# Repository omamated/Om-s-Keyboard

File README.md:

# My Keyboard

- A custom low-profile wireless mechanical keyboard designed from scratch to match the coolness of the Apple Magic Keyboard while teaching me PCB design, firmware development, and CAD. I know it looks pretty simple, but it took me a long time to make it and I'm pretty proud of it

## Overview

This keyboard is a mechanical and wireless built with the Nice!Nano V2 microcontroller and will use ZMK firmware. My idea was to create a minimal keyboard that matches my dad's MacBook Pro which I occasionally use.

Instead of buying an existing keyboard, I decided to design it myself, so I could learn software like Kicad and Fusion360 more.

The keyboard features:

* Bluetooth connectivity using ZMK firmware
* Nice!Nano V2 controller
* Hot-swappable switches
* Custom Pikachu-themed 3D-printed enclosure
* Rechargeable battery 10000 mah
* Low-profile design

# Why I Built This

I've been using a basic keyboard for a long time and wanted something that felt more premium and minimalist. I wanted something that wasn't that bulky, but still stood out, so I designed the pikachu minamalist keyboard. This keyboard helped me learn major software for the laptop I'm building in the future.

# The Process

## PCB Design

The PCB was designed in KiCad.

Since I was still kinda new to KiCad, I spent a lot of time learning footprint selection, routing techniques, and manufacturing requirements. The PCB includes a way for me to charge a battery using the Nice!Nano. The PCB also uses a matrix to make all the switches fit. 

### Final PCB image

## Schematic Design

The schematic wasn't that bad for me to do as I learned a decent amount from my macropad, so I didn't spend most of my time here. Most of my time was spent on finding the right symbols. I later learned that the symbol doesn't matter at all if you have the right footprint.

### Final Schematic images

## Case Design

The enclosure was designed in Fusion 360. My initial design was very basic, practically just a box with screws.

### Version 2

After reviewing the first version, I increased the case thickness and improved the mounting system. I added thicker walls as the thin walls would lead to snapping.

### Version 3 
Made the case a whole pikachu theme, I will print this in yellow to make it something unique to me. I also added a honey comb pattern at the bottom. To me, this was by far the best version and the one I'm the most proud of.

# Manufacturing Plan

The keyboard will be assembled using the following process. You will first need to order the PCB and all of the otherb parts in the BOM. Once you recieve all the parts and the PCB, you can start soldering them all and then you can flash ZMK software onto the Nice!Nano. Once thats working you can assemble the case, which means you need to put the heat inserts and screw it together.

# Problems

This project made me learn plenty of things that I didn't know very well before.

### Learning KiCad

Although I had some previous experience creating a macropad, this wass my first PCB project without a tutorial

### Routing the PCB

I had to route the PCB about 5 times as it was very confusing to do.

# What I Learned

Through this project I learned how to use PCB design softwares better, how to use ZMK, and how to use fusion 360 efficiently.

# Resources

The following resources were especially helpful during development:

### PCB Design

https://www.youtube.com/watch?v=7UXsD7nSfDY

### Keyboard Design

ScottO'KeeBs YouTube Channel

### Software
 I used Kicad, Fusion360, and ZMK

---

# Bill of Materials
(links are in BOM.csv)

| Item                       | Cost      | Quantity                    |
| -------------------------- | --------- | --------------------------- |
| Low Profile Switches       | $15       | 80                          |
| Nice!Nano V2               | $25       | 1                           |
| Diodes                     | $6        | 80 (only packs of ten)      |
| Custom Keyboard PCB        | $30       | 1 (Minimum order is 5)      |
| Hot-swap Sockets           | $12       | 80                          |
| Power Switch               | $1.50     | 1 (minimum order is 2)      |
| Battery Jack               | $1        | 1 (minimum order is 2)      |
| Battery                    | $7        | 1                           |
| Filament for Case          | $20       | 1                           |
| Heat Inserts & Screws      | $8        | 1 (M2.5 should work)        |

Estimated Total: $136 (before tax + Shipping)

---

# Future Improvements

Potential future upgrades include:

* CNC (I think) enclosure
* Magnetic charging system (maybe for me to use in a custom laptop I'm designing?)
* Lower-profile enclosure revisions
* Improved battery mounting
* Custom keycaps

# Gallery/Images

### PCB Render

Although it is quite tight the hot-swap pocket does fit under the Nice nano, which I anticipated as per my resources.

### Schematic

### Updated Case

### Zine Page

Ok look, my Zine was saved in canva (under my school account), so it was hard for me to add the new case on the back side, so I hope y'all will let it slide.

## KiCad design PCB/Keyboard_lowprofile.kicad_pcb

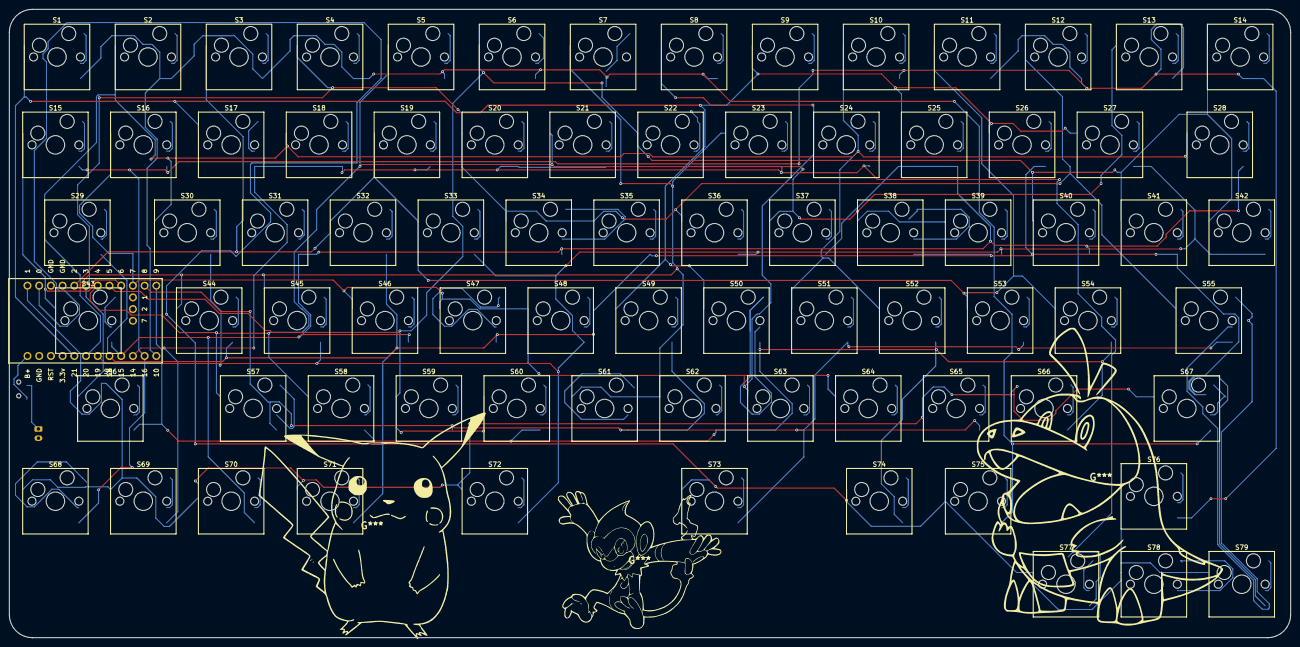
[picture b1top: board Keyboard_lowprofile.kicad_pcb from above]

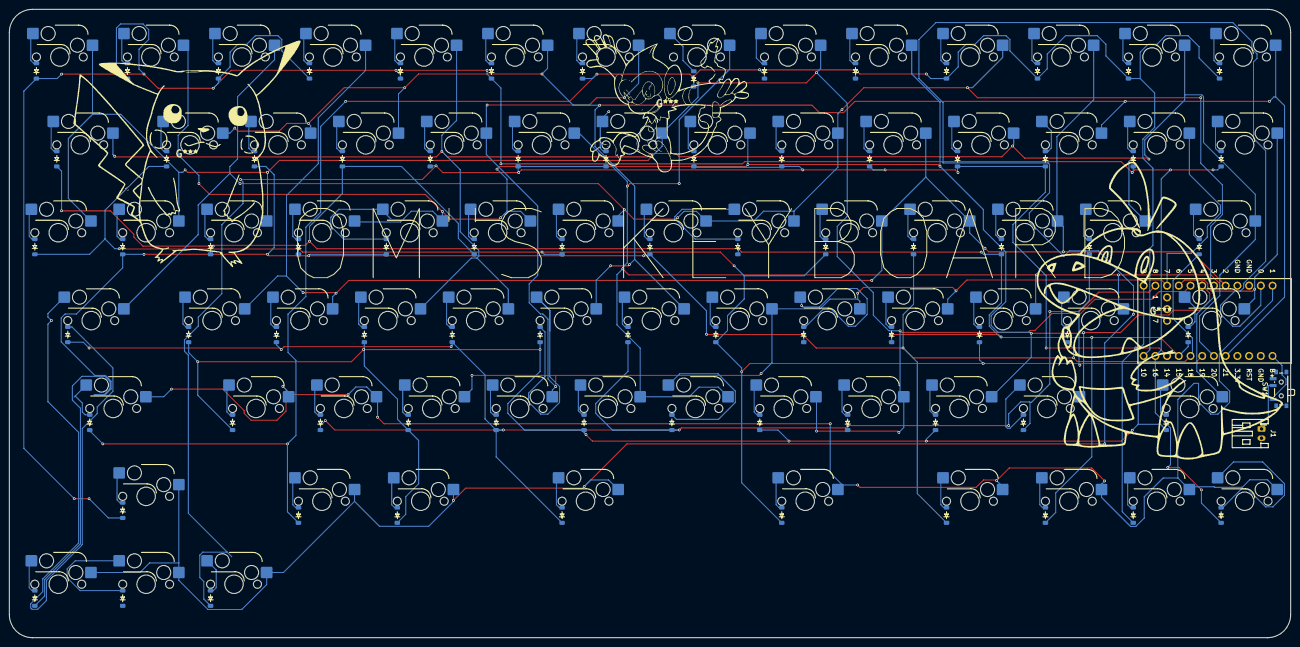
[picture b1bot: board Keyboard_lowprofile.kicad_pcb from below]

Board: 2 copper layers, 277.8 x 136.2 mm, 161 parts (82 on the bottom side), 99 nets.

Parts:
D1, D2, D3, D4, D5, D6, D7, D8, D9, D10, D11, D12, D13, D14, D15, D16, D17, D18, D19, D20, D21, D22, D23, D24, D25, D26, D27, D28, D29, D30, D31, D32, D33, D34, D35, D36, D37, D38, D39, D40, D41, D42, D43, D44, D45, D46, D47, D48, D49, D50, D51, D52, D53, D54, D55, D56, D57, D58, D59, D60, D61, D62, D63, D64, D65, D66, D67, D68, D69, D70, D71, D72, D73, D74, D75, D76, D77, D78, D79: Diode_SOD-123
J1: Conn_01x02_Socket; JST_PH_S2B-PH-K_1x02_P2.00mm_Horizontal
S1, S2, S3, S4, S5, S6, S7, S8, S9, S10, S11, S12, S13, S14, S15, S16, S17, S18, S19, S20, S21, S22, S23, S24, S25, S26, S27, S28, S29, S30, S31, S32, S33, S34, S35, S36, S37, S38, S39, S40, S41, S42, S43, S44, S45, S46, S47, S48, S49, S50, S51, S52, S53, S54, S55, S56, S57, S58, S59, S60, S61, S62, S63, S64, S65, S66, S67, S68, S69, S70, S71, S72, S73, S74, S75, S76, S77, S78, S79: Hotswap_MX_1.00u
SW1: SW_SPDT_312; SW_SPDT_PCM12
U1: Nice_Nano_V2

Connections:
Column 0: S1.1, S9.1, S17.1, S25.1, S26.1, S27.1, S49.1, S50.1, U1.20 (21)
Column 1: S2.1, S10.1, S18.1, S28.1, S29.1, S30.1, S51.1, S52.1, U1.19 (20)
Column 2: S3.1, S11.1, S19.1, S31.1, S32.1, S33.1, S53.1, S54.1, U1.5 (2)
Column 3: S4.1, S12.1, S20.1, S34.1, S35.1, S36.1, S55.1, S56.1, U1.6 (3)
Column 4: S5.1, S13.1, S21.1, S37.1, S38.1, S39.1, S57.1, S58.1, U1.7 (4)
Column 5: S6.1, S14.1, S22.1, S40.1, S41.1, S42.1, S59.1, S60.1, U1.8 (5)
Column 6: S7.1, S15.1, S23.1, S43.1, S44.1, S45.1, S61.1, S62.1, U1.9 (6)
Column 7: S8.1, S16.1, S24.1, S46.1, S47.1, S48.1, S63.1, S64.1, U1.10 (7)
Column 8: S65.1, S66.1, S67.1, S68.1, S69.1, S70.1, S71.1, S72.1, U1.1
Column 9: S73.1, S74.1, S75.1, S76.1, S77.1, S78.1, S79.1, U1.2 (0)
unnamed: D1.2 (A), S1.2
unnamed: D2.2 (A), S2.2
unnamed: D3.2 (A), S3.2
unnamed: D4.2 (A), S4.2
unnamed: D5.2 (A), S5.2
unnamed: D6.2 (A), S6.2
unnamed: D7.2 (A), S7.2
unnamed: D8.2 (A), S8.2
unnamed: D9.2 (A), S9.2
unnamed: D10.2 (A), S10.2
unnamed: D11.2 (A), S11.2
unnamed: D12.2 (A), S12.2
unnamed: D13.2 (A), S13.2
unnamed: D14.2 (A), S14.2
unnamed: D15.2 (A), S15.2
unnamed: D16.2 (A), S16.2
unnamed: D17.2 (A), S17.2
unnamed: D18.2 (A), S18.2
unnamed: D19.2 (A), S19.2
unnamed: D20.2 (A), S20.2
unnamed: D21.2 (A), S21.2
unnamed: D22.2 (A), S22.2
unnamed: D23.2 (A), S23.2
unnamed: D24.2 (A), S24.2
unnamed: D25.2 (A), S25.2
unnamed: D26.2 (A), S26.2
unnamed: D27.2 (A), S27.2
unnamed: D28.2 (A), S28.2
unnamed: D29.2 (A), S29.2
unnamed: D30.2 (A), S30.2
unnamed: D31.2 (A), S31.2
unnamed: D32.2 (A), S32.2
unnamed: D33.2 (A), S33.2
unnamed: D34.2 (A), S34.2
unnamed: D35.2 (A), S35.2
unnamed: D36.2 (A), S36.2
unnamed: D37.2 (A), S37.2
unnamed: D38.2 (A), S38.2
unnamed: D39.2 (A), S39.2
unnamed: D40.2 (A), S40.2
unnamed: D41.2 (A), S41.2
unnamed: D42.2 (A), S42.2
unnamed: D43.2 (A), S43.2
unnamed: D44.2 (A), S44.2
unnamed: D45.2 (A), S45.2
unnamed: D46.2 (A), S46.2
unnamed: D47.2 (A), S47.2
unnamed: D48.2 (A), S48.2
unnamed: D49.2 (A), S49.2
unnamed: D50.2 (A), S50.2
unnamed: D51.2 (A), S51.2
unnamed: D52.2 (A), S52.2
unnamed: D53.2 (A), S53.2
unnamed: D54.2 (A), S54.2
unnamed: D55.2 (A), S55.2
unnamed: D56.2 (A), S56.2
unnamed: D57.2 (A), S57.2
unnamed: D58.2 (A), S58.2
unnamed: D59.2 (A), S59.2
unnamed: D60.2 (A), S60.2
unnamed: D61.2 (A), S61.2
unnamed: D62.2 (A), S62.2
unnamed: D63.2 (A), S63.2
unnamed: D64.2 (A), S64.2
unnamed: D65.2 (A), S65.2
unnamed: D66.2 (A), S66.2
unnamed: D67.2 (A), S67.2
unnamed: D68.2 (A), S68.2
unnamed: D69.2 (A), S69.2
unnamed: D70.2 (A), S70.2
unnamed: D71.2 (A), S71.2
unnamed: D72.2 (A), S72.2
unnamed: D73.2 (A), S73.2
unnamed: D74.2 (A), S74.2
unnamed: D75.2 (A), S75.2
unnamed: D76.2 (A), S76.2
unnamed: D77.2 (A), S77.2
unnamed: D78.2 (A), S78.2
unnamed: D79.2 (A), S79.2
unnamed: J1.1, SW1.2 (C)
unnamed: SW1.1 (B), U1.24 (B+)
Row 0: D49.1 (K), D51.1 (K), D53.1 (K), D55.1 (K), D57.1 (K), D59.1 (K), D61.1 (K), D63.1 (K), D65.1 (K), D73.1 (K), U1.11 (8)
Row 1: D50.1 (K), D52.1 (K), D54.1 (K), D56.1 (K), D58.1 (K), D60.1 (K), D62.1 (K), D64.1 (K), D66.1 (K), D74.1 (K), U1.12 (9)
Row 2: D1.1 (K), D2.1 (K), D3.1 (K), D4.1 (K), D5.1 (K), D6.1 (K), D7.1 (K), D8.1 (K), D67.1 (K), D75.1 (K), U1.13 (10)
Row 3: D9.1 (K), D10.1 (K), D11.1 (K), D12.1 (K), D13.1 (K), D14.1 (K), D15.1 (K), D16.1 (K), D68.1 (K), D76.1 (K), U1.14 (16)
Row 4: D17.1 (K), D18.1 (K), D19.1 (K), D20.1 (K), D21.1 (K), D22.1 (K), D23.1 (K), D24.1 (K), D69.1 (K), D77.1 (K), U1.15 (14)
Row 5: D25.1 (K), D28.1 (K), D31.1 (K), D34.1 (K), D37.1 (K), D40.1 (K), D43.1 (K), D46.1 (K), D70.1 (K), U1.16 (15)
Row 6: D26.1 (K), D29.1 (K), D32.1 (K), D35.1 (K), D38.1 (K), D41.1 (K), D44.1 (K), D47.1 (K), D71.1 (K), D79.1 (K), U1.17 (18)
Row 7: D27.1 (K), D30.1 (K), D33.1 (K), D36.1 (K), D39.1 (K), D42.1 (K), D45.1 (K), D48.1 (K), D72.1 (K), U1.18 (19)

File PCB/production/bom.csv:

Designator,Footprint,Quantity,Value,LCSC Part #
"D1, D10, D11, D12, D13, D14, D15, D16, D17, D18, D19, D2, D20, D21, D22, D23, D24, D25, D26, D27, D28, D29, D3, D30, D31, D32, D33, D34, D35, D36, D37, D38, D39, D4, D40, D41, D42, D43, D44, D45, D46, D47, D48, D49, D5, D50, D51, D52, D53, D54, D55, D56, D57, D58, D59, D6, D60, D61, D62, D63, D64, D65, D66, D67, D68, D69, D7, D70, D71, D72, D73, D74, D75, D76, D77, D78, D79, D8, D9",Diode_SOD-123,79,~,
J1,JST_PH_S2B-PH-K_1x02_P2.00mm_Horizontal,1,Conn_01x02_Socket,
"S1, S10, S11, S12, S13, S14, S15, S16, S17, S18, S19, S2, S20, S21, S22, S23, S24, S25, S26, S27, S28, S29, S3, S30, S31, S32, S33, S34, S35, S36, S37, S38, S39, S4, S40, S41, S42, S43, S44, S45, S46, S47, S48, S49, S5, S50, S51, S52, S53, S54, S55, S56, S57, S58, S59, S6, S60, S61, S62, S63, S64, S65, S66, S67, S68, S69, S7, S70, S71, S72, S73, S74, S75, S76, S77, S78, S79, S8, S9",Hotswap_MX_1.00u,79,~,
SW1,SW_SPDT_PCM12,1,SW_SPDT_312,
U1,Nice_Nano_V2,1,Nice_Nano_V2,

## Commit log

2026-02-01 Update README with project details and parts list
    Expanded the project description and added a detailed bill of parts with links and prices.
2026-02-01 Refactor links in README for consistency
    Updated links in the README to use a consistent format.
2026-02-01 Update README to include bill of parts section
    Added a section for the bill of parts with a link.
2026-02-01 Fix link formatting in README.md
2026-02-01 Update link text for design document in README
2026-02-01 Create sadf
2026-02-01 PCB Files
2026-02-01 Add images for final PCB and schematic
    Added images for final PCB, schematic, and 3D viewer.
2026-02-01 Gerber file
2026-02-01 Create adsf
2026-02-01 Add Fusion 360 case image to README
    Added an image of the Fusion 360 case to the README.
2026-02-07 Fix tutorial links formatting in README
    Corrected formatting issues with tutorial links in the README.
2026-02-07 Fix links in README.md for tutorials
2026-02-07 Fix link formatting for scottokeebs in README
2026-02-07 Update README with project completion details
    Added personal experience and time taken for project completion.
2026-02-21 Add ZMK configuration for keyboard layout
2026-02-21 added files
2026-02-21 BBOM
2026-02-22 changed cad
2026-02-22 Revise README with assembly details and formatting
    Updated the README to include planned assembly details and improved formatting.
2026-02-28 Add item list with costs and links to README
2026-02-28 Add BOM with item details and costs
2026-02-28 Update README.md file with new content
2026-03-21 better cad
    ADDED SCREW HOLES
2026-03-27 added source files
2026-03-27 added images to readme for screwholes in the case
2026-03-31 Readem fixed
2026-03-31 images in readme
2026-03-31 Updated CAD Full Assembly
    Wouldn't led me do F3d for a full assembly did F3z instead
2026-03-31 organized
2026-04-19 Add link to Wireless Magic Keyboard PDF
2026-04-19 Update README with new resources and images
2026-04-25 Update battery link to AliExpress
2026-04-25 ZMK config fully addded
2026-04-25 Update BOM table in README to match BOM.csv data
2026-04-25 Revert battery link back to AliExpress
2026-04-25 Update BOM.csv to use AliExpress battery link
2026-05-10 Zine
2026-05-10 V0 gone
2026-05-10 Modify BOM.csv to add Quantity columnfew
    Updated BOM.csv to include Quantity column.
2026-05-10 added new bom(better)
2026-05-10 Revise Bill of Materials format and total cost
    Updated the Bill of Materials section with new format and corrected total cost.
2026-05-10 Update Bill of Materials to proper markdown table format with all columns
2026-05-22 Revise README for V2 and add images
    Updated description of V2 changes and added new images.
2026-05-22 Update image in README.mdf
    Replaced an image in the README with a new one and removed an old image.
2026-05-22 Update README with new images and descriptions
    Added new images and updated descriptions for the keyboard project.
2026-05-22 Update README with new images and case details
    Added new images and updated the case description in README.
2026-05-22 Update BOM.csv to add new items and fix formatting
2026-05-22 Update BOM.csv with new total and item quantities
    Updated BOM.csv to reflect new total cost and item quantities.
2026-05-22 zine1
2026-05-22 Update Zine page link to newly uploaded PDF
2026-05-22 Fix link and add image in README
    Updated the link for the 'Wireless Magic Keyboard' PDF and added a new image.
2026-05-22 Update BOM.csv to add new items and correct format
2026-05-22 Modify BOM.csv with new items and updated total
    Updated total cost and added new items to BOM.
2026-05-22 Add Case to BOM and update total cost
2026-05-26 update CAD
2026-06-18 Enhance README with project details and images
    Expanded the README to provide a detailed overview of the keyboard project, including design goals, features, manufacturing plans, and challenges faced during development.
2026-06-18 Enhance README with design preference details
    Added a personal note about the keyboard's design preference.
2026-06-18 Add Zine Page section to README
    Add a new section for Zine Page with an image.
2026-06-23 Update BOM.csv to include new item links
2026-06-23 Update BOM.csv with new items and costs
2026-06-23 Update BOM.csv with new item entries
2026-06-23 Add link reference to BOM.csv in README
2026-06-23 Update BOM.csv with revised item details
    Updated BOM with new item costs and links.
2026-06-23 Updated cad with a better case
2026-06-23 Update README with version 3 case design and images
    Added new images and updated the case design description for version 3.
2026-06-23 Update images in README.md
    Replaced old images with updated versions and adjusted sizes.
2026-06-23 Revise README for enhanced project overview
    Updated project description for clarity and detail.
2026-06-24 Add new Zine image to READMEnew zine
2026-06-24 new zine added
2026-06-24 Update README with Zine note
    Added a note about the Zine being saved in Canva and its limitations.
2026-06-26 Revise README for keyboard project details
    Updated the README to reflect changes in keyboard design, features, and manufacturing process. Improved clarity and added new sections for gallery and future improvements.
2026-06-28 Add note on hot-swap pocket compatibility
    Added a note about the hot-swap pocket fitting under the Nice nano.
2026-06-28 Fixed routes added silkscreen checked if Nice!nano Fits
